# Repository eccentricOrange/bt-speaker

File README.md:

# Speaker Driver

This is a simple analog speaker driver, mostly driven simply by the goal of learning more about this field.

## Features

### Cross-over filtration
The driver is designed to support two drivers, one for bass and one for treble. The cross-over frequency is **1326 Hz**, and is achieved by using simple first order filters.

*   Capacitor: 10 uF
*   Resistor: 12R

### Voltage pre-amplification
The input voltage is amplified by a factor of 6, using a simple non-inverting amplifier (LM741 op-amp). It is expected that the input voltage is around **1 V amplitude (2 Vpp)**, delivered by a 3.5 mm audio connector.

*   Input resistor: 820R
*   Fixed feedback resistor: 10k
*   Variable feedback resistor: 10k (in parallel with the fixed resistor)

### Power amplification
The next stage is a power amplifier, which is a simple class AB amplifier, that allows each driver to draw up to about **5W**. Each driver is expected to have an impedance of **4 Ohm**. TIP31 and TIP32 power transistors are used.

### Power supply
The PCB takes a single 24VDC 1A barrel jack input, and divides the voltage into 12VDC and -12VDC using a simple voltage divider.

## Result
The final assembled two-way speaker system with custom PCB is shown below

## Future work
*   Miniaturize the PCB, using at least SMD components, if not a pre-made amplifier IC.
*   Understand, measure, and reduce the signal-to-noise ratio.
*   Use dedicated battery control circuitry for portable use.
*   Add Bluetooth connectivity (ideally BLE), using a microcontroller.
    *   Ideally, use custom firmware and design a custom antenna on the PCB.
    *   Alternatively, use an ESP32 module with a pre-made antenna.
*   Use buttons for power ON/OFF, volume control, and Bluetooth pairing.

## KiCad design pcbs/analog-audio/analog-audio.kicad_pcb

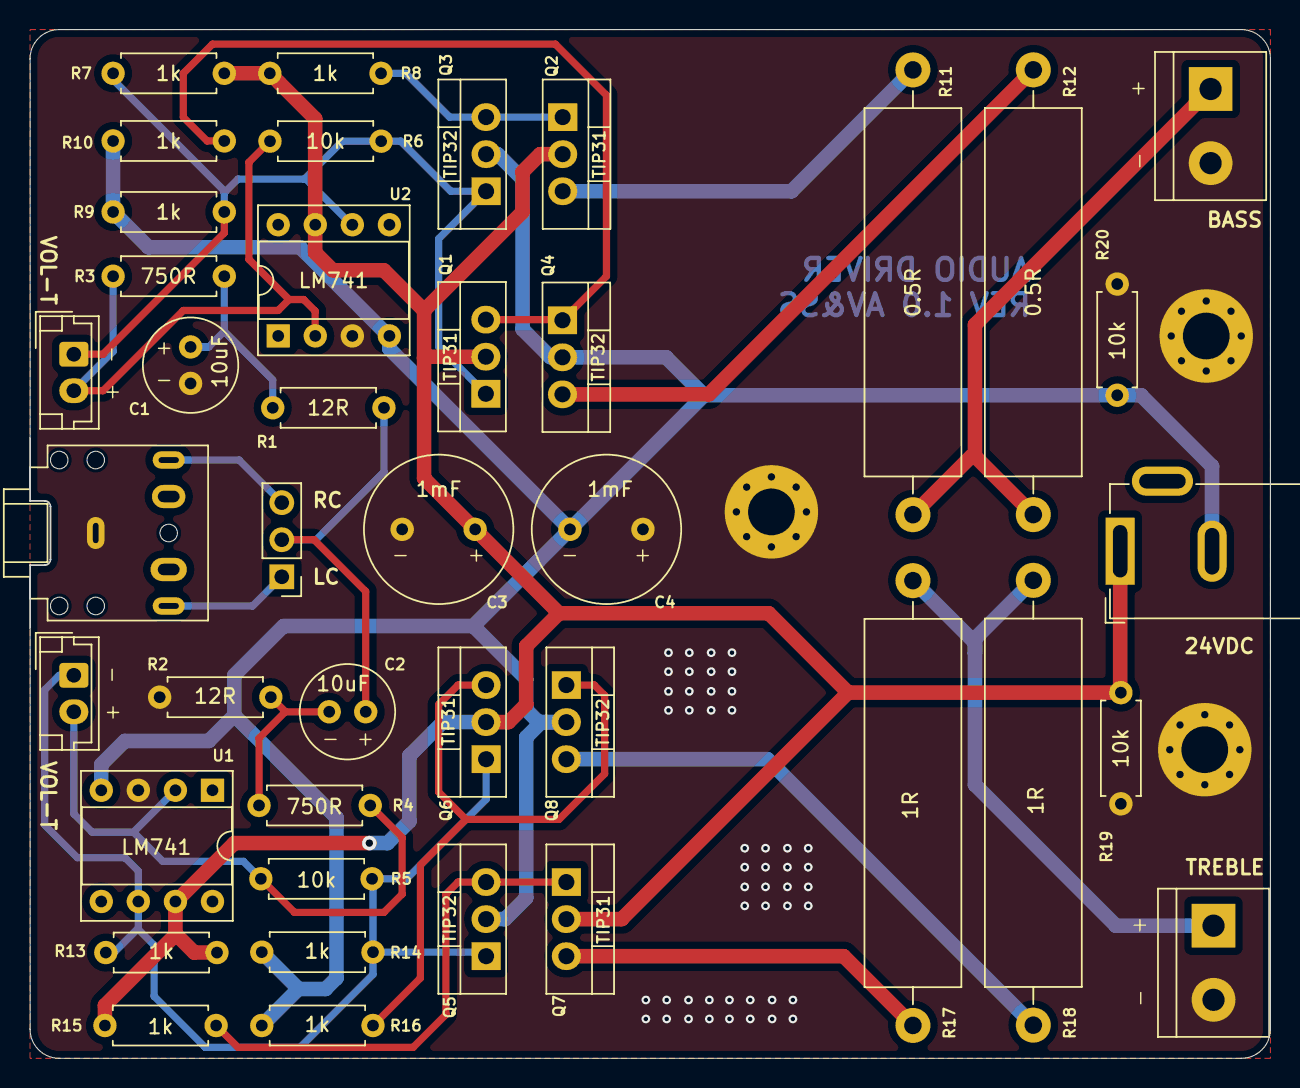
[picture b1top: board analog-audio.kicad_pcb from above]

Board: 2 copper layers, 85.0 x 70.4 mm, 44 parts (0 on the bottom side), 22 nets.

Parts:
C1, C2: 10uF; C_Radial_D6.3mm_H11.0mm_P2.50mm
C3, C4: 1mF; C_Radial_D10.0mm_H12.5mm_P5.00mm
H1, H2, H3: MountingHole_Pad; MountingHole_3.2mm_M3_Pad_Via
J1: AudioJack5; Jack_3.5mm_CUI_SJ1-3525N_Horizontal
J2: 24VDC; BarrelJack_GCT_DCJ200-10-A_Horizontal
J3, J4: VOL-T; JST_EH_B2B-EH-A_1x02_P2.50mm_Vertical
J5: BASS; TerminalBlock_bornier-2_P5.08mm
J6: TREBLE; TerminalBlock_bornier-2_P5.08mm
J7: Channel; PinHeader_1x03_P2.54mm_Vertical
Q1, Q2, Q6, Q7: TIP31; TO-220-3_Vertical
Q3, Q4, Q5, Q8: TIP32; TO-220-3_Vertical
R1, R2: 12R; R_Axial_DIN0207_L6.3mm_D2.5mm_P7.62mm_Horizontal
R3, R4: 750R; R_Axial_DIN0207_L6.3mm_D2.5mm_P7.62mm_Horizontal
R5, R6, R19, R20: 10k; R_Axial_DIN0207_L6.3mm_D2.5mm_P7.62mm_Horizontal
R7, R8, R9, R10, R13, R14, R15, R16: 1k; R_Axial_DIN0207_L6.3mm_D2.5mm_P7.62mm_Horizontal
R11, R12: 0.5R; R_Axial_Power_L25.0mm_W6.4mm_P30.48mm
R17, R18: 1R; R_Axial_Power_L25.0mm_W6.4mm_P30.48mm
U1, U2: LM741; DIP-8_W7.62mm_Socket

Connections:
0: C1.1, C3.2, C4.1, H1.1, H2.1, H3.1, J1.S, J5.2, J6.2, R2.2, R19.2, R20.1, U1.3 (+), U2.3 (+)
+12V: C3.1, J2.1, Q1.2 (C), Q2.2 (C), Q6.2 (C), Q7.2 (C), R7.1, R8.1, R13.1, R15.1, R19.1, U1.7 (V+), U2.7 (V+)
-12V: C4.2, J2.2, Q3.2 (C), Q4.2 (C), Q5.2 (C), Q8.2 (C), R9.2, R10.2, R14.2, R16.2, R20.2, U1.4 (V-), U2.4 (V-)
L: J1.T, J7.1
unnamed: J3.2, R4.2, R5.1, U1.2 (-)
unnamed: J4.2, R3.2, R6.1, U2.2 (-)
unnamed: Q1.3 (E), Q4.1 (B), R10.1
unnamed: Q2.1 (B), Q3.3 (E), R8.2
unnamed: Q2.3 (E), R11.1
unnamed: Q4.3 (E), R12.2
unnamed: Q5.3 (E), Q7.1 (B), R15.2
unnamed: Q6.3 (E), Q8.1 (B), R16.1
unnamed: Q7.3 (E), R17.1
unnamed: Q8.3 (E), R18.2
R: J1.R1, J7.3
VBASS: J5.1, R11.2, R12.1
VHPF: C2.2, R2.1, R4.1
VHPF_PA: J3.1, Q5.1 (B), Q6.1 (B), R5.2, R13.2, R14.1, U1.6
VLPF: C1.2, R1.2, R3.1
VLPF_PA: J4.1, Q1.1 (B), Q3.1 (B), R6.2, R7.2, R9.1, U2.6
VTREBLE: J6.1, R17.2, R18.1
Vs: C2.1, J7.2, R1.1

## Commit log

2024-03-28 set kicad path
2024-03-29 re-designed for power
2024-03-29 added volume control
2024-03-29 clean up schematic
2024-03-30 re-routed
2024-03-30 successful sims?
2024-03-31 successful sims!!
2024-03-31 vias and +- silkscreen
2024-04-01 add mounting holes
2024-04-01 readme
2024-04-01 silkscreen
2024-04-24 start report
2024-04-24 done-something
2024-04-24 report updates
2024-04-24 editor
2024-04-26 rm report
2024-05-25 fixed simulations and updated schematic for real values
2024-05-25 fixed error in PCB and updated to use real values
2025-05-22 fix heading level
